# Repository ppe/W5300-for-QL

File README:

Hardware design and drivers for Sinclair QL experimental ethernet card.

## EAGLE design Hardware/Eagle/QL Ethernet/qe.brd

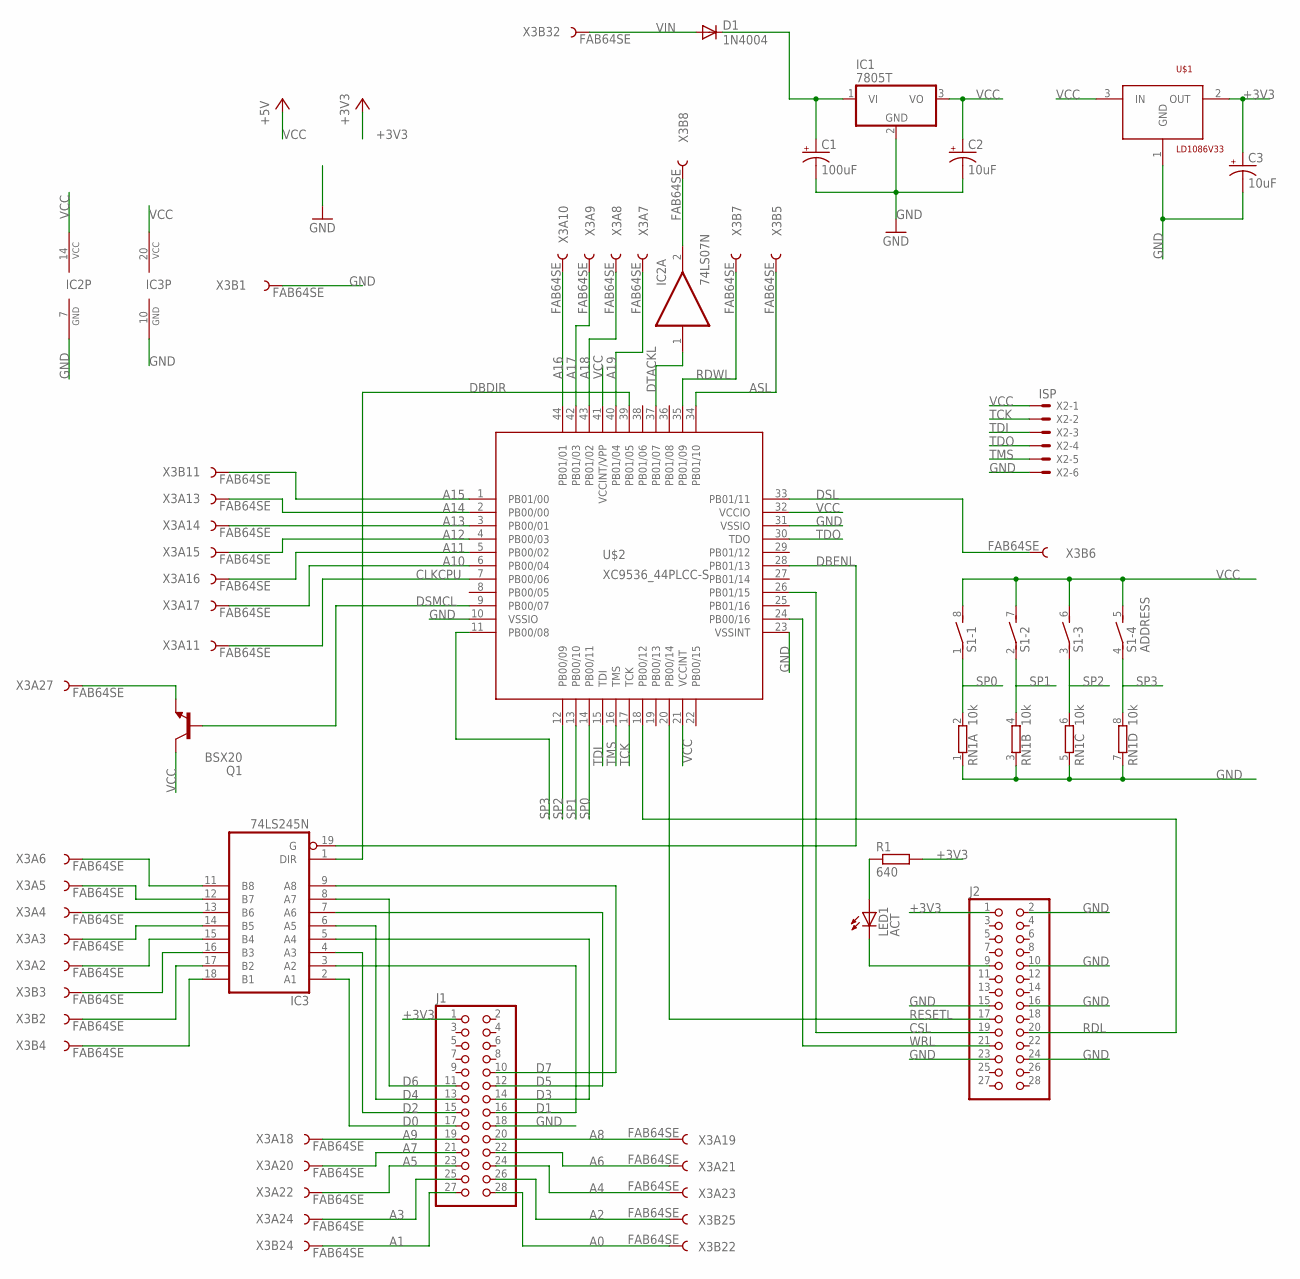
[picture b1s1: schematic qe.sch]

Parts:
C1: 100uF; TAP5-80
C2, C3: 10uF; TAP5-45
D1: 1N4004; DO41-10
IC1: 7805T; TO220H
IC2: 74LS07N; DIL14
IC3: 74LS245N; DIL20
J1, J2: PINHD-2X14; 2X14
LED1: ACT; LED5MM
Q1: BSX20; TO18
R1: 640; 0204/7
RN1: 10k; SIL8
S1: ADDRESS; DIP04S
U$1: LD1086V33; TO220
U$2: XC9536_44PLCC-S; PLCC44-S
X2: ISP; 22-23-2061
X3: FAB64SE; FAB64S

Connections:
+3V3: C3.+, J1.1, J2.1, R1.2, U$1.2 (OUT)
A0: J1.28, X3.B22
A1: J1.27, X3.B24
A2: J1.26, X3.B25
A3: J1.25, X3.A24
A4: J1.24, X3.A23
A5: J1.23, X3.A22
A6: J1.22, X3.A21
A7: J1.21, X3.A20
A8: J1.20, X3.A19
A9: J1.19, X3.A18
A10: U$2.6 (PB00/04), X3.A17
A11: U$2.5 (PB00/02), X3.A16
A12: U$2.4 (PB00/03), X3.A15
A13: U$2.3 (PB00/01), X3.A14
A14: U$2.2 (PB00/00), X3.A13
A15: U$2.1 (PB01/00), X3.B11
A16: U$2.44 (PB01/01), X3.A10
A17: U$2.42 (PB01/03), X3.A9
A18: U$2.43 (PB01/02), X3.A8
A19: U$2.40 (PB01/04), X3.A7
ASL: U$2.34 (PB01/10), X3.B5
CLKCPU: U$2.7 (PB00/06), X3.A11
CSL: J2.19, U$2.26 (PB01/15)
D0: IC3.2 (A1), J1.17
D1: IC3.3 (A2), J1.16
D2: IC3.4 (A3), J1.15
D3: IC3.5 (A4), J1.14
D4: IC3.6 (A5), J1.13
D5: IC3.7 (A6), J1.12
D6: IC3.8 (A7), J1.11
D7: IC3.9 (A8), J1.10
DBDIR: IC3.1 (DIR), U$2.39 (PB01/05)
DBENL: IC3.19 (G), U$2.28 (PB01/13)
DSL: U$2.33 (PB01/11), X3.B6
DSMCL: Q1.2 (B), U$2.9 (PB00/07)
DTACKL: IC2.1 (I), U$2.37 (PB01/07)
GND: C1.-, C2.-, C3.-, IC1.2 (GND), IC2.7 (GND), IC3.10 (GND), J1.18, J2.2, J2.10, J2.15, J2.16, J2.23, J2.24, RN1.1, RN1.3 (1), RN1.5 (1), RN1.7 (1), U$1.1 (GND), U$2.10 (VSSIO), U$2.23 (VSSINT), U$2.31 (VSSIO), X2.6, X3.B1
unnamed: IC3.11 (B8), X3.A6
unnamed: IC3.12 (B7), X3.A5
unnamed: IC3.13 (B6), X3.A4
unnamed: IC3.14 (B5), X3.A3
unnamed: IC3.15 (B4), X3.A2
unnamed: IC3.16 (B3), X3.B3
unnamed: IC3.17 (B2), X3.B2
unnamed: IC3.18 (B1), X3.B4
unnamed: Q1.1 (E), X3.A27
unnamed: J2.9, LED1.K (C)
unnamed: LED1.A, R1.1
unnamed: D1.A, X3.B32
unnamed: IC2.2 (O), X3.B8
RDL: J2.20, U$2.18 (PB00/12)
RDWL: U$2.35 (PB01/09), X3.B7
RESETL: J2.17, U$2.20 (PB00/14)
SP0: RN1.2, S1.1, U$2.14 (PB00/11)
SP1: RN1.4 (2), S1.2 (1), U$2.13 (PB00/10)
SP2: RN1.6 (2), S1.3 (1), U$2.12 (PB00/09)
SP3: RN1.8 (2), S1.4 (1), U$2.11 (PB00/08)
TCK: U$2.17 (TCK), X2.2
TDI: U$2.15 (TDI), X2.3
TDO: U$2.30 (TDO), X2.4
TMS: U$2.16 (TMS), X2.5
VCC: C2.+, IC1.3 (VO), IC2.14 (VCC), IC3.20 (VCC), Q1.3 (C), S1.5 (2), S1.6 (2), S1.7 (2), S1.8 (2), U$1.3 (IN), U$2.21 (VCCINT), U$2.32 (VCCIO), U$2.41 (VCCINT/VPP), X2.1
VIN: C1.+, D1.C, IC1.1 (VI)
WRL: J2.21, U$2.24 (PB00/16)

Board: 2 copper layers, 18 parts (0 on the bottom side), 65 nets, no tracks yet.

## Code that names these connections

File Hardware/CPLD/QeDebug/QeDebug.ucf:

#PACE: Start of Constraints generated by PACE

#PACE: Start of PACE I/O Pin Assignments
NET "address<0>"  LOC = "P6" | BUFG = DATA_GATE ; 
NET "address<1>"  LOC = "P5" | BUFG = DATA_GATE ; 
NET "address<2>"  LOC = "P4"  ; 
NET "address<3>"  LOC = "P3"  ; 
NET "address<4>"  LOC = "P2"  ; 
NET "address<5>"  LOC = "P1"  ; 
NET "address<6>"  LOC = "P44"  ; 
NET "address<7>"  LOC = "P43"  ; 
NET "address<8>"  LOC = "P42"  ; 
NET "address<9>"  LOC = "P40"  ; 
NET "asl"  LOC = "P34"  ; 
NET "clk"  LOC = "P7" | BUFG = CLK  ;
NET "dbdir"  LOC = "P39"  ; 
NET "dbenl"  LOC = "P28"  ; 
NET "dsl"  LOC = "P33"  ; 
NET "dsmcl"  LOC = "P9"  ; 
NET "dtackl"  LOC = "P37"  ; 
NET "rdwl"  LOC = "P35"  ; 
NET "wizcsl"  LOC = "P26"  ; 
NET "wizrdl"  LOC = "P18"  ; 
NET "wizrstl"  LOC = "P20"  ; 
NET "wizwrl"  LOC = "P24"  ; 

#PACE: Start of PACE Area Constraints

#PACE: Start of PACE Prohibit Constraints

#PACE: End of Constraints generated by PACE

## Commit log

2011-02-27 Initial version (work in progress) of the DNS name resolver
2011-02-28 Initial import of W5300 specific code and start of device driver
2011-03-01 Driver name comparison work. Added the missing constatnts file
2011-03-01 Testing.
2011-03-01 Added number detection logic.
2011-03-02 Added a routine to test and read a byte value from string.
2011-03-02 Split test code to separate file
2011-03-02 Added an ip address parsing function.
2011-03-08 Generalized number parser. Replaced byte parser with new implementation.
2011-03-08 Added driver name parser that recognizes udp driver names with a numeric ip address and port
2011-03-20 Added nslookup superbasic extension. Currently it only creates a buffer that contains the dns query message.
2011-03-20 Added socket open code to socket layer
2012-01-19 WIP on prototype circuit board
2012-01-20 Initial (old) version of CPLD design files.
2012-01-20 Added ISP header and its connections to XC9536.
2012-02-22 First working version of nslookup.
2012-02-22 Restructured code to be more readable. Actual lookup refactored to be a standalone function.
2012-02-22 Extracted a separate resolver module.
2012-02-22 Ntpdate v1 without time zone support.
2012-02-22 Added missing free for malloc.
2012-02-26 First successful TCP test.
2012-02-27 Simplified version of address control for debugging purposes.
2012-02-27 Added Xilinx ISE ignores.
2012-09-18 Added a short project description.
2014-01-22 Add i2c and spi test code to debug project.
2014-01-23 wget_c: Modified server IP address.
2014-01-23 Add pseudocode for wget http header parsing.
2014-01-23 Change base address of w5300 address space.
2014-01-23 Add Eagle 6.4 schematics for the prototype adapter.
2014-01-23 Add library for the 3.3V regulator part used on the prototype board.
2014-01-23 Added comments to parser for better readability.
2014-01-24 Add stub for reading and resolving host name if no ip address given.
2014-01-25 Added hostname extraction routine to use for resolver call.
2014-01-26 Add LF line ending policy to .gitattributes.
2014-01-26 Fix syntax.
2014-01-26 Change include file device name to be parameterized.
2014-01-27 Fix return code for open call when driver name does not match.
2014-01-27 Fix driver name pointer on return from host name parse.
2014-03-26 Refactor driver name parsing code.
2014-04-02 Refactor address to dns format translation and add test harness.
2014-04-02 Add expectation verification to resolver test.
2014-04-05 Resolver: query buffers are now correctly populated.
2014-04-05 Resolver: add function to skip over names
2014-04-05 Resolver: add parse ip from response packet.
2014-10-19 Add initial version of SuperBASIC monitor program to examine status of W5300
2014-10-20 fix wrong function call in dst mac display
2014-11-17 Change address range to 2000 and remove address select.
2014-11-17 Remove ASL gating and rely on DSL instead.
2014-11-17 Change base addressess to C8000 (card) and C9000 (reset)
2014-11-17 Set output slew rate to slow
2014-11-17 Fix W5300 reset logic and add test for it.
2014-11-17 Fix gating, ack and dsmcl logic.
2014-11-17 Fix misunderstood timing and signalling for W5300. Best version so far
2014-11-17 Change gating: synchronize with clk to comply with 68k bus cycle specification.
2014-11-18 Resolver gethostbyname first checks if the host string is a dotted ip address.
2014-11-20 WIP http_client send and recv works, resp parsing broken
    Lots of other string handling broken also.
2014-12-01 WIP on http_client. Succesful receive of small text file.
2014-12-01 Rudimentary W5300 monitor basic program. Requires TK2.
2014-12-06 Remove test printf.
2014-12-06 wget: initial set of files
2014-12-09 wget: first working version
2014-12-31 WIP: start working on new version of driver
2015-01-06 Add memory allocation for channel open/close.
2015-01-07 QE_UNLOAD unloads driver and releases allocated heap.
2015-01-08 Add stub function for nslookup keyword in driver
2015-01-09 Add parameter handling to nslookup$ function.
2015-01-09 Change odd/even test in nslookup$
2015-01-09 Change way to clear A0.
2015-01-11 Stub trap #3 handler for gethostbyname.
2015-01-11 Refactor: extract get_driver_info helper function to use from keywords.
2015-01-11 add parameter validation to nslookup$ function, remove debug print to #0.
2015-01-11 Refactor get_driver_info: extract open/close routines for sck_ channel.
2015-01-11 Add to NSLOOKUP$: copy parameter to driver temporary buffer.
2015-01-11 Add user heap initialization to driver init.
2015-01-11 Change NSLOOKUP$: copy parameter to user heap block instead of static buffer.
2015-01-12 Change NSLOOKUP$: use LINK and frame pointer for local variable storage.
2015-01-13 remove old code. fix keyword table because of long extension names.
2015-01-13 NSLOOKUP$: add heap allocation for temporary struct hostent.
2015-01-13 NSLOOKUP$: fix heap allocation block size bug.
2015-01-13 NSLOOKUP$: fix bug clearing maths heap on exit Bug came up on Minerva, D2 is added to BV_RIP but the high word of the register may have rubbish in it thus mangling the maths stack.
2015-01-14 NSLOOKUP$: add cleanup code when hostent alloc fails.
2015-01-14 Refactor get_driver_info, pull out open/close SCK_ channel.
2015-01-14 NSLOOKUP$ refactor error and exit handling.
2015-01-14 NSLOOKUP$: add call to gethostbyname
2015-01-14 NSLOOKUP$ fix user heap allocation and pointer bug.
2015-01-15 gethostbyname: add static stub implementation that partially fills the struct hostent.
2015-01-15 gethostbyname: populate address family and bytes per address fields in struct hostent
2015-01-16 WIP: add inet_ntoa call.
2015-01-17 inet_ntoa impelementation
2015-01-17 nslookup$ use results from gethostbyname. TODO: change stack-based frame pointer to a user heap based one.
2015-01-18 Fix ntoa bug, channel id was not preserved in a0 through the call.
2015-01-18 NSLOOKUP$: fix return value handling on minerva.
2015-01-18 Add stub inet_aton implementation.
2015-01-18 inet_aton: add call to read ip address.
2015-01-19 gethostbyname: for an ip address, return a hostent with address as hostname and ip.
2015-01-20 gethostbyname: test user heap allocation from within the io handler.
2015-01-20 gethostbyname: create DNS query buffer and release it.
2015-01-21 gethostbyname: add dummy fixed dns response packet and call to parse it.
2015-01-22 dns response parser: fix answer skip logic
2015-01-22 parse dns response: fix syntax errors
2015-01-22 gethostbyname: return answer from captured packet.
2015-01-22 WIP: proper parsing of DNS response packet.
2015-01-23 WIP parse dns response: process stack now sets up CNAME and A tables in struct hostent.
2015-01-24 dns response parser: add copy hostname from first A resource.
2015-01-25 resolv: pick ip addresses from dns response and populate them in struct hostent.
2015-01-25 nslookup$: pick first ip address from struct hostent as return value
2015-01-26 response parser: parse aliases into struct hostent
2015-01-26 response parser: remove trailing '.' from names and aliases.
2015-01-27 Add return value generation in dns response parsing.
2015-01-28 Add W5300 HW layer file and call HW init from driver init.
2015-01-29 driver init: initialize a socket reservation table in driver linkage block.
2015-01-29 gethostbyname: change local vars to use frame pointer in preparation for socket reservation code.
2015-01-29 gethostbyname: fix user heap deallocation bug.
2015-01-30 gethostbyname: add socket reservation to lookup
2015-01-30 gethostbyname: add release socket reservation.
2015-01-31 w5300: add open routine for UDP sockets. Support ERR_NC and continuation.
2015-02-01 gethostbyname and w5300 continuation mechanism WIP.
2015-02-01 Add socket close operation.
2015-02-01 Fix bug filling struct hostent when query address is an ip.
2015-02-01 Change function call name
2015-02-01 Close and release sockets when closing channel and/or starting new IO op on channel after timeout.
2015-02-02 Add stub sendto implementation.
2015-02-03 Add _list and _rel files to .gitignore to prepare for qmac assembler
2015-02-03 Change w5300_asm source to qmac assembler format.
2015-02-03 Add skeleton makefile for driver.
2015-02-04 Rename w5300 include file.
2015-02-04 Add make dependency to include file.
2015-02-04 Change resolv_asm to Qmac asm format.
2015-02-04 Makefile: add dependency to resolv_asm.
2015-02-04 Change parser_asm to Qmac asm format.
2015-02-04 Makefile: add dependency to parser_asm.
2015-02-05 Change driver_asm to qmac format.
2015-02-05 Makefile: add dependency to driver_asm
2015-02-05 Makefile: add linking instruction for driver target.
2015-02-05 Add linker _map files to .gitignore.
2015-02-06 Small makefile fix
2015-02-07 Add stub to set destination for a socket.
2015-02-08 Fix the routine to write bytes to a socket.
2015-02-08 Refactor w5300-specific sendto code into w5300 module.
2015-02-08 WIP on HW layer sendto implementation.
2015-02-09 Add logic to open a UDP socket (without destination info).
2015-02-09 Add sendto implementation scaffolding to IOSS layer.
2015-02-10 Fix W5300 buffer write.
2015-02-10 Fix socket close sending wrong command to W5300.
2015-02-11 Fix socket number parameter in socket close.
2015-02-11 Fix sendok check logic in sendto.
2015-02-12 Add stub for recvfrom implementation.
2015-02-13 WIP: add recvfrom w5300 implementation.
2015-02-14 WIP on read bytes from socket.
2015-02-15 WIP on recvfrom: fix bug in odd-byte reads.
2015-02-15 recvfrom: add unaligned target buffer logic.
2015-02-16 add recvfrom parameter check
2015-02-17 Add received bytes # check to recvfrom.
2015-02-18 add call to w5300 impelementation code from recvfrom.
2015-02-19 Add FIFO buffer copy to w5300 recvfrom implementation.
2015-02-19 W5300 recvfrom: mark the packet as received after copying through FIFO.
2016-04-21 Ignore _o files
2016-04-21 Add (partly broken) prototype irc client
2016-04-21 Refactor driver to be hybrid c/asm driver
2016-11-10 Add gitattributes file to define file extensions for languages not automatically picked up by GitHub (probably due to non-standard file extension)
2016-11-10 gitattributes fix, move linguist-language definitions to root
2023-01-12 PCB Rev 1
